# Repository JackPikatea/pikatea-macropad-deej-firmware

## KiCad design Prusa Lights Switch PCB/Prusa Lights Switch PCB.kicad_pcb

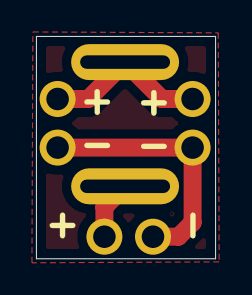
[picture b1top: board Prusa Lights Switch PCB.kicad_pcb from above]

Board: 2 copper layers, 10.0 x 12.3 mm, 4 parts (0 on the bottom side), 3 nets.

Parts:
J1, J2, J3: 2 Pin larger header holes
SW1: Prusa Light Switch

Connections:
unnamed: J1.1, J2.1, SW1.1
unnamed: J1.2, J2.2, J3.2
unnamed: J3.1, SW1.2
